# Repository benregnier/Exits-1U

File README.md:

# Exits

4hp DIY eurorack line and headphone output module based on [Exits](https://github.com/ramphands/Exits) which is in part based on [Nearness](https://github.com/sarnesjo/nearness) and [Forestcaver headphone amp](https://github.com/forestcaver/Analog-Voice/tree/master/AJH_Headphone_Amp) designs. 

The Nearness section is a "minimal panning mixer for the Eurorack modular synthesizer system. Seven inputs, two outputs. The closer an input is to an output, the greater its influence on it."  

This design makes the following changes:
- Changed to a 1U format
- Reestablishes front panel L and R outputs
- In lieu of a stereo 1/4 main out, has a six-pin connector that is compatible with Intellijel cases.
- NE5532 in lieu of NJM4556 for the headphone portion

## Schematic and PCBs

The [kicad](Kicad) directory contains the schematic and PCB layout as a KiCad 6 project.

## Panel

Available in the [panel](Panel) directory as a PDF and an SVG vector file as well as PCB design and gerbers.

## Intellijel Output Pinout

This module has a six pin connector on the back meant to be compatible with outputs on Intellijel and Befaco cases. Pinouts match per the diagram below. Outputs are not balanced.  Note that if you want to mount this module on the far right hand side of the case both the output and power ribbon cables need to be low-profile.  

## License

[CC BY-SA 4.0](http://creativecommons.org/licenses/by-sa/4.0/)

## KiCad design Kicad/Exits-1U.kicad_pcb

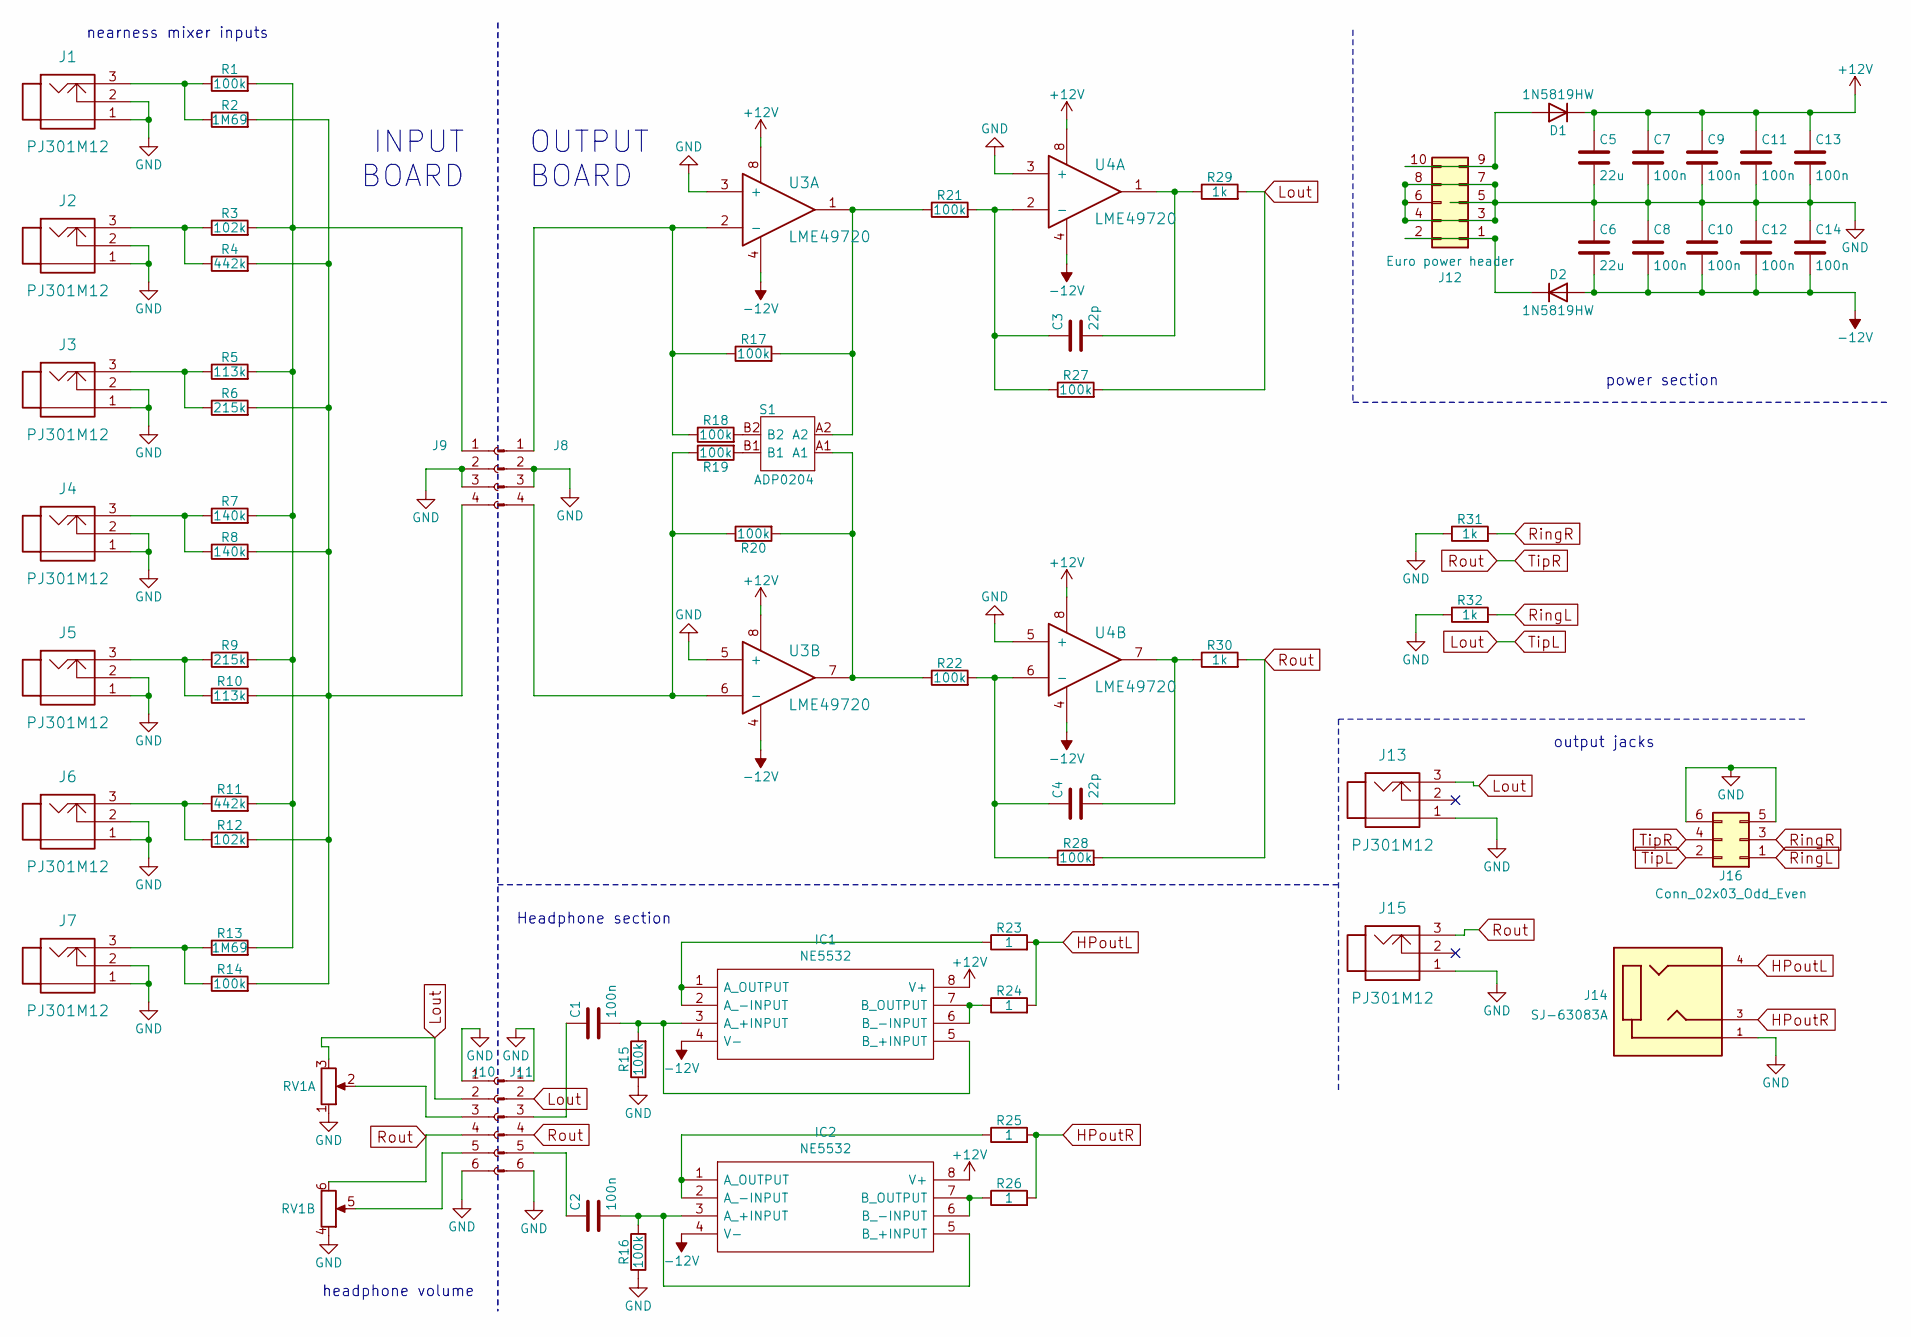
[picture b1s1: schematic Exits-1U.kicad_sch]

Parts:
C1, C2, C7, C8, C9, C10, C11, C12, C13, C14: 100n; C_0805_2012Metric_Pad1.18x1.45mm_HandSolder
C3, C4: 22p; C_0805_2012Metric_Pad1.18x1.45mm_HandSolder
C5, C6: 22u; C_Elec_5x5.8
D1, D2: 1N5819HW; D_SOD-123
IC1: NE5532; SOIC-8_3.9x4.9mm_P1.27mm; Manufacturer_Part_Number NE5532
IC2: NE5532; SOIC-8_3.9x4.9mm_P1.27mm; Mouser Part Number 513-NJM4556AV-TE1
J1, J2, J3, J4, J5, J6, J7, J13, J15: PJ301M12
J8: Conn_01x04_Male; PinHeader_1x04_P2.54mm_Vertical
J9: Conn_01x04_Female; PinSocket_1x04_P2.54mm_Vertical
J10: Conn_01x06_Female; PinSocket_1x06_P2.54mm_Vertical
J11: Conn_01x06_Male; PinHeader_1x06_P2.54mm_Vertical
J12: Euro power header; IDC-Header_2x05_P2.54mm_Vertical
J14: SJ-63083A; CUI_SJ-63083A; PARTREV 1.0
J16: Conn_02x03_Odd_Even; PinHeader_2x03_P2.54mm_Vertical
R1, R14, R15, R16, R17, R18, R19, R20, R21, R22, R27, R28: 100k; R_0805_2012Metric_Pad1.20x1.40mm_HandSolder
R2, R13: 1M69; R_0805_2012Metric_Pad1.20x1.40mm_HandSolder
R3, R12: 102k; R_0805_2012Metric_Pad1.20x1.40mm_HandSolder
R4, R11: 442k; R_0805_2012Metric_Pad1.20x1.40mm_HandSolder
R5, R10: 113k; R_0805_2012Metric_Pad1.20x1.40mm_HandSolder
R6, R9: 215k; R_0805_2012Metric_Pad1.20x1.40mm_HandSolder
R7, R8: 140k; R_0805_2012Metric_Pad1.20x1.40mm_HandSolder
R23, R24, R25, R26: 1; R_0805_2012Metric_Pad1.20x1.40mm_HandSolder
R29, R30, R31, R32: 1k; R_0805_2012Metric_Pad1.20x1.40mm_HandSolder
RV1: 50k A; Potentiometer_Alpha_RD902F-40-00D_Dual_Vertical
S1: ADP0204; Mouser Part Number 506-ADP0204
U3, U4: LME49720; SOIC-8_3.9x4.9mm_P1.27mm

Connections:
+12V: C5.1, C7.1, C9.1, C11.1, C13.1, D1.1 (K), IC1.8 (V+), IC2.8 (V+), U3.8, U4.8
-12V: C6.2, C8.2, C10.2, C12.2, C14.2, D2.2 (A), IC1.4 (V-), IC2.4 (V-), U3.4, U4.4
GND: C5.2, C6.1, C7.2, C8.1, C9.2, C10.1, C11.2, C12.1, C13.2, C14.1, J1.1, J1.2, J2.1, J2.2, J3.1, J3.2, J4.1, J4.2, J5.1, J5.2, J6.1, J6.2, J7.1, J7.2, J8.2, J8.3, J9.2, J9.3, J10.1, J10.6, J11.1, J11.6, J12.3, J12.4, J12.5, J12.6, J12.7, J12.8, J13.1, J14.1, J15.1, J16.5, J16.6, R15.1, R16.1, R31.1, R32.1, RV1.1, RV1.4, U3.3 (+), U3.5 (+), U4.3 (+), U4.5 (+)
HPoutL: J14.4, R23.2, R24.2
HPoutR: J14.3, R25.2, R26.2
Lout: J10.2, J11.2, J13.3, J16.2, R27.2, R29.2, RV1.3
unnamed: C3.2, R29.1, U4.1
unnamed: C4.2, R30.1, U4.7
unnamed: D1.2 (A), J12.9, J12.10
unnamed: D2.1 (K), J12.1, J12.2
unnamed: C1.2, IC1.3 (A_+INPUT), IC1.5 (B_+INPUT), R15.2
unnamed: IC1.1 (A_OUTPUT), IC1.2 (A_-INPUT), R23.1
unnamed: IC1.6 (B_-INPUT), IC1.7 (B_OUTPUT), R24.1
unnamed: C2.2, IC2.3 (A_+INPUT), IC2.5 (B_+INPUT), R16.2
unnamed: IC2.1 (A_OUTPUT), IC2.2 (A_-INPUT), R25.1
unnamed: IC2.6 (B_-INPUT), IC2.7 (B_OUTPUT), R26.1
unnamed: J1.3, R1.1, R2.1
unnamed: J2.3, R3.1, R4.1
unnamed: J3.3, R5.1, R6.1
unnamed: J4.3, R7.1, R8.1
unnamed: J5.3, R9.1, R10.1
unnamed: J6.3, R11.1, R12.1
unnamed: J7.3, R13.1, R14.1
unnamed: J8.1, R17.1, R18.1, U3.2 (-)
unnamed: J8.4, R19.1, R20.1, U3.6 (-)
unnamed: J9.1, R1.2, R3.2, R5.2, R7.2, R9.2, R11.2, R13.2
unnamed: J9.4, R2.2, R4.2, R6.2, R8.2, R10.2, R12.2, R14.2
unnamed: J10.3, RV1.2
unnamed: J10.5, RV1.5
unnamed: C1.1, J11.3
unnamed: C2.1, J11.5
unnamed: R17.2, R21.1, S1.A2, U3.1
unnamed: R18.2, S1.B2
unnamed: R19.2, S1.B1
unnamed: R20.2, R22.1, S1.A1, U3.7
unnamed: C3.1, R21.2, R27.1, U4.2 (-)
unnamed: C4.1, R22.2, R28.1, U4.6 (-)
RingL: J16.1, R32.2
RingR: J16.3, R31.2
Rout: J10.4, J11.4, J15.3, J16.4, R28.2, R30.2, RV1.6

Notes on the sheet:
headphone volume
INPUT BOARD
Headphone section
OUTPUT BOARD
output jacks
nearness mixer inputs
power section

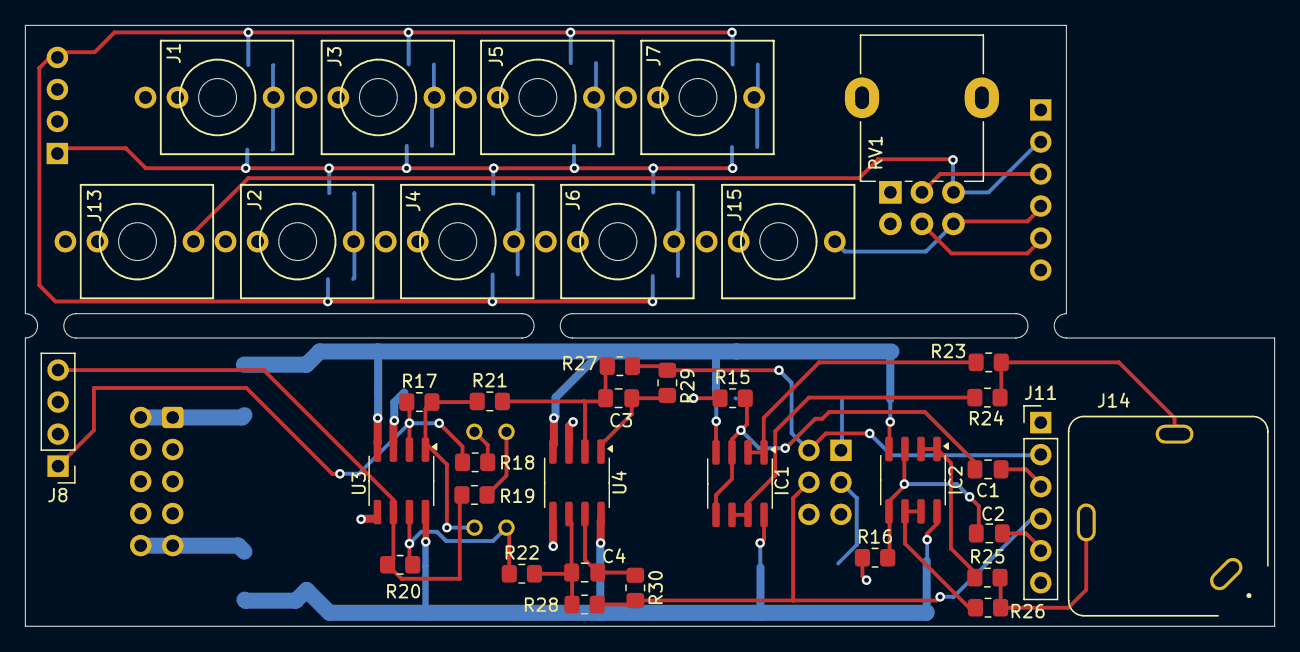
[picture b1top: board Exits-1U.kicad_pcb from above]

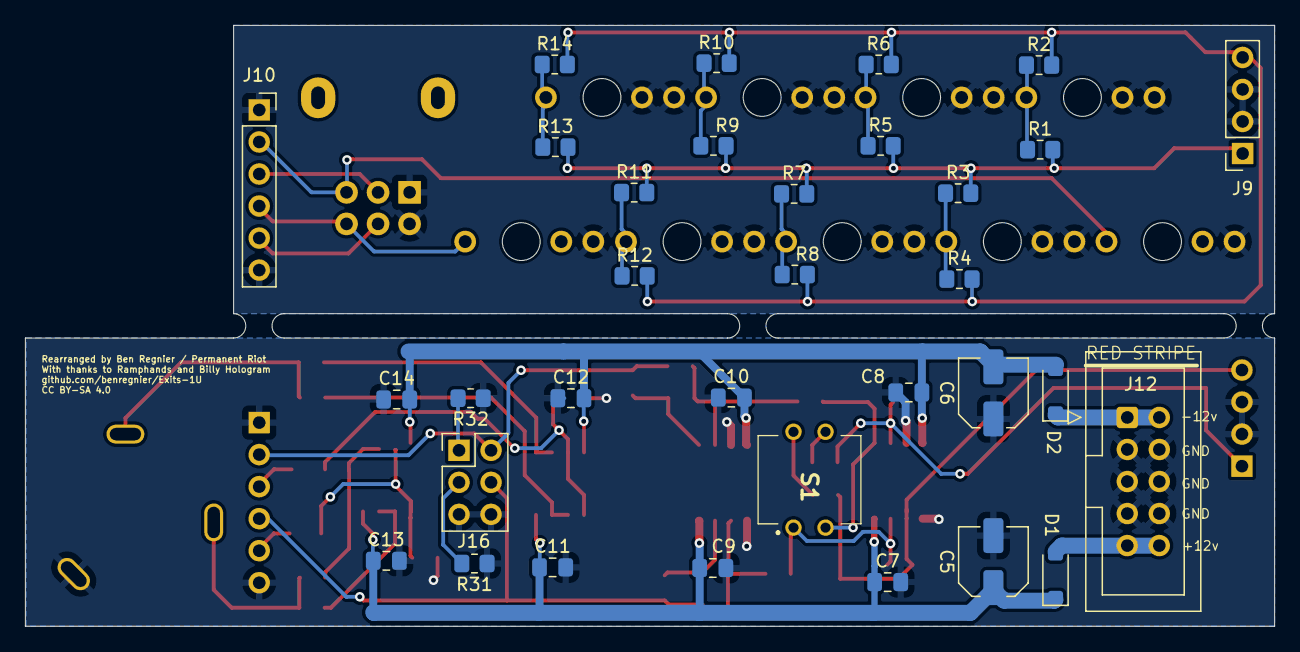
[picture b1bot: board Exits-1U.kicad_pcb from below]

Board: 2 copper layers, 99.1 x 47.7 mm, 70 parts (33 on the bottom side), 40 nets.

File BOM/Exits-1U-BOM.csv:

"Id";"Designator";"Footprint";"Quantity";"Designation";"Supplier and ref";
1;"IC2,IC1";"SOIC-8_3.9x4.9mm_P1.27mm";2;"NE5532";;;
2;"J2,J13,J1,J15,J6,J3,J4,J5,J7";"PJ301M12";9;"PJ301M12";;;
3;"U4,U3";"SOIC-8_3.9x4.9mm_P1.27mm";2;"LME49720";;;
4;"R17,R27,R28,R19,R15,R16,R20,R21,R18,R22,R1,R14";"R_0805_2012Metric_Pad1.20x1.40mm_HandSolder";12;"100k";;;
5;"RV1";"Potentiometer_Alpha_RD902F-40-00D_Dual_Vertical";1;"50k A";;;
6;"C4,C3";"C_0805_2012Metric_Pad1.18x1.45mm_HandSolder";2;"22p";;;
7;"R23,R25,R26,R24";"R_0805_2012Metric_Pad1.20x1.40mm_HandSolder";4;"1";;;
8;"J14";"CUI_SJ-63083A";1;"SJ-63083A";;;
9;"R30,R29,R31,R32";"R_0805_2012Metric_Pad1.20x1.40mm_HandSolder";4;"1k";;;
10;"C2,C1,C8,C14,C13,C9,C12,C10,C7,C11";"C_0805_2012Metric_Pad1.18x1.45mm_HandSolder";10;"100n";;;
11;"J8";"PinHeader_1x04_P2.54mm_Vertical";1;"Conn_01x04_Male";;;
12;"J11";"PinHeader_1x06_P2.54mm_Vertical";1;"Conn_01x06_Male";;;
13;"C6,C5";"C_Elec_5x5.8";2;"22u";;;
14;"R9,R6";"R_0805_2012Metric_Pad1.20x1.40mm_HandSolder";2;"215k";;;
15;"J10";"PinSocket_1x06_P2.54mm_Vertical";1;"Conn_01x06_Female";;;
16;"J16";"PinHeader_2x03_P2.54mm_Vertical";1;"Conn_02x03_Odd_Even";;;
17;"J12";"IDC-Header_2x05_P2.54mm_Vertical";1;"Euro power header";;;
18;"R8,R7";"R_0805_2012Metric_Pad1.20x1.40mm_HandSolder";2;"140k";;;
19;"S1";"ADP0204";1;"ADP0204";;;
20;"R10,R5";"R_0805_2012Metric_Pad1.20x1.40mm_HandSolder";2;"113k";;;
21;"D1,D2";"D_SOD-123";2;"1N5819HW";;;
22;"J9";"PinSocket_1x04_P2.54mm_Vertical";1;"Conn_01x04_Female";;;
23;"R11,R4";"R_0805_2012Metric_Pad1.20x1.40mm_HandSolder";2;"442k";;;
24;"R13,R2";"R_0805_2012Metric_Pad1.20x1.40mm_HandSolder";2;"1M69";;;
25;"R12,R3";"R_0805_2012Metric_Pad1.20x1.40mm_HandSolder";2;"102k";;;

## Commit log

2025-05-17 Create images
2025-05-17 Rename Exits 1U Panel.jpg to images/Exits 1U Panel.jpg
